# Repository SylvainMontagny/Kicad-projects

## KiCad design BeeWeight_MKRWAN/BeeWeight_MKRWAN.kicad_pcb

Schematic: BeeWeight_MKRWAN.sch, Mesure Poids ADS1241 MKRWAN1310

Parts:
C1, C2, C3, C4, C5, C6, C7, C8: 10nF; C_0603_1608Metric_Pad1.05x0.95mm_HandSolder
C9, C10, C11, C12, C13: 100nF; C_0603_1608Metric_Pad1.05x0.95mm_HandSolder
C14, C15: 18pF; C_0603_1608Metric_Pad1.05x0.95mm_HandSolder
C16: 100n; C_0603_1608Metric_Pad1.05x0.95mm_HandSolder
J2, J3, J4, J5: 691412120004B; TermBlock_1x04_P3.50mm Wurth_691412120004B; PART-NUMBER 691412120004B
J6: Conn_01x02_Male; PinHeader_1x02_P2.54mm_Horizontal
J7, J8: Conn_01x14_Female; PinSocket_1x14_P2.54mm_Vertical
J9: 694108301002; Jack_DC_2.1mm Wurth_694108301002; PART-NUMBER 694108301002
JP1: SolderJumper_2_Open; SolderJumper-2_P1.3mm_Open_RoundedPad1.0x1.5mm
Q1: IRLML6244; SOT-23
R1, R5: 1M; R_0805_2012Metric_Pad1.15x1.40mm_HandSolder
R2: 560k; R_0805_2012Metric_Pad1.15x1.40mm_HandSolder
R3: 100k; R_0805_2012Metric_Pad1.15x1.40mm_HandSolder
R4: 330k; R_0805_2012Metric_Pad1.15x1.40mm_HandSolder
R6: 4.7k; R_0805_2012Metric_Pad1.15x1.40mm_HandSolder
U1: ADS1241
U2: DS18B20; TO-92
Y1: Crystal; Crystal-4Mhz-TH-Wurth-830027298B

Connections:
/3V3: C10.2, C11.2, C12.2, C16.2, J2.1, J3.1, J4.1, J5.1, J8.12, R6.2, U1.1, U1.5, U1.9, U1.21, U2.3 (VDD)
/5V: J8.14
/A0_D15_3V7_BAT: C13.1, J7.2, R4.2, R5.1
/A1_D16_Vin: C9.1, J7.3, R2.1, R3.2
/A2_D17: J7.4
/A3_D19: J7.5
/A4_D19: J7.6
/A5_D20: J7.7
/A6_D21: J7.8
/AIN0: C5.1, J5.3, U1.11
/AIN1: C1.1, J5.4, U1.12
/AIN2: C4.1, J4.3, U1.17
/AIN3: C8.1, J4.4, U1.18
/AIN4: C2.1, J2.3, U1.13
/AIN5: C6.1, J2.4, U1.14
/AIN6: C3.1, J3.3, U1.15
/AIN7: C7.1, J3.4, U1.16
/AREF: J7.1
/D0: J7.9
/D1_PDWN: J7.10, U1.7
/D2_DRDY: J7.11, U1.27
/D3_CMD_MOS: J7.12, Q1.1 (G), R1.2
/D4_DS1820_DQ: J7.13, R6.1, U2.2 (DQ)
/D5: J7.14
/D6_USER_LED: J8.1
/D7_CS: J8.2, U1.23
/D8_MOSI: J8.3, U1.24
/D9_SCLK: J8.4, U1.26
/D10_MISO: J8.5, U1.25
/D11_SDA: J8.6
/D12_SCL: J8.7
/D13_RX: J8.8
/D14_TX: J8.9
/GND_LowPower: J2.2, J3.2, J4.2, J5.2, JP1.1, Q1.3 (D), U2.1 (GND)
/RESET: J8.10
/Vin: J8.13, J9.1, R2.2
GND: C1.2, C2.2, C3.2, C4.2, C5.2, C6.2, C7.2, C8.2, C9.2, C10.1, C11.1, C12.1, C13.2, C14.1, C15.2, C16.1, J8.11, J9.2, JP1.2, Q1.2 (S), R1.1, R3.1, R5.2, U1.2, U1.10, U1.19, U1.20, U1.22, U1.28
unnamed: C14.2, U1.3, Y1.1
unnamed: C15.1, U1.4, Y1.2
unnamed: J6.1, J6.2, R4.1

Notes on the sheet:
External Power Supply - Solar Panel
Weight Scale Input
Battery level measurement
Low Power management
Temperature Sensor
ADC and MKRWAN Connector

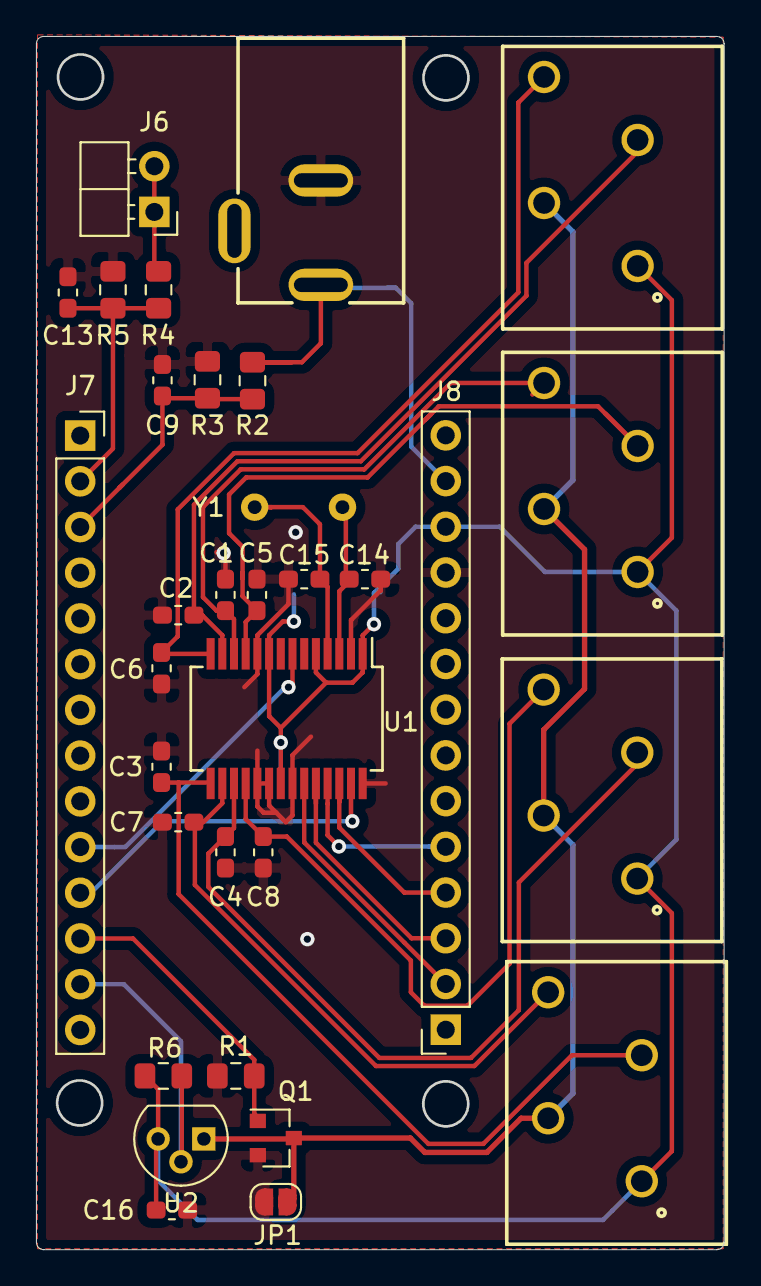
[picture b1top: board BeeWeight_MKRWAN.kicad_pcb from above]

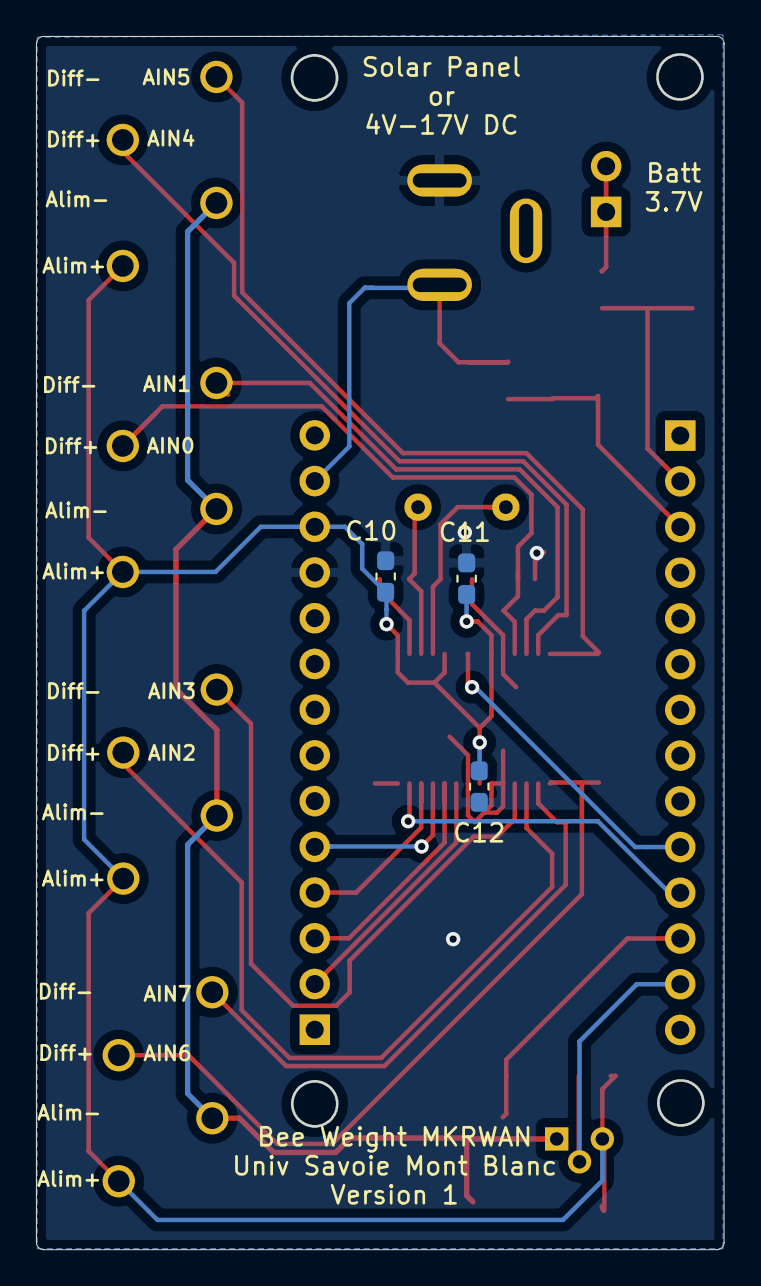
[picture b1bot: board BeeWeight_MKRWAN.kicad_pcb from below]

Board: 2 copper layers, 38.1 x 67.3 mm, 35 parts (3 on the bottom side), 25 nets.

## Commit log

2021-05-05 Initial Release
2021-05-06 Update Crystal Footprint
2021-05-10 Minor changes in schematic and PCB
2021-05-11 Nouveau routage par G.Manusset
2021-05-11 Update DS18B20 Footprint
    Otherwise eurocircuit fees are based on class 8 PCB
